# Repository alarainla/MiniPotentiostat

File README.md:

# MiniPotentiostat
This is repository for minimalistic open-source potentiostat for electrochemical sensing

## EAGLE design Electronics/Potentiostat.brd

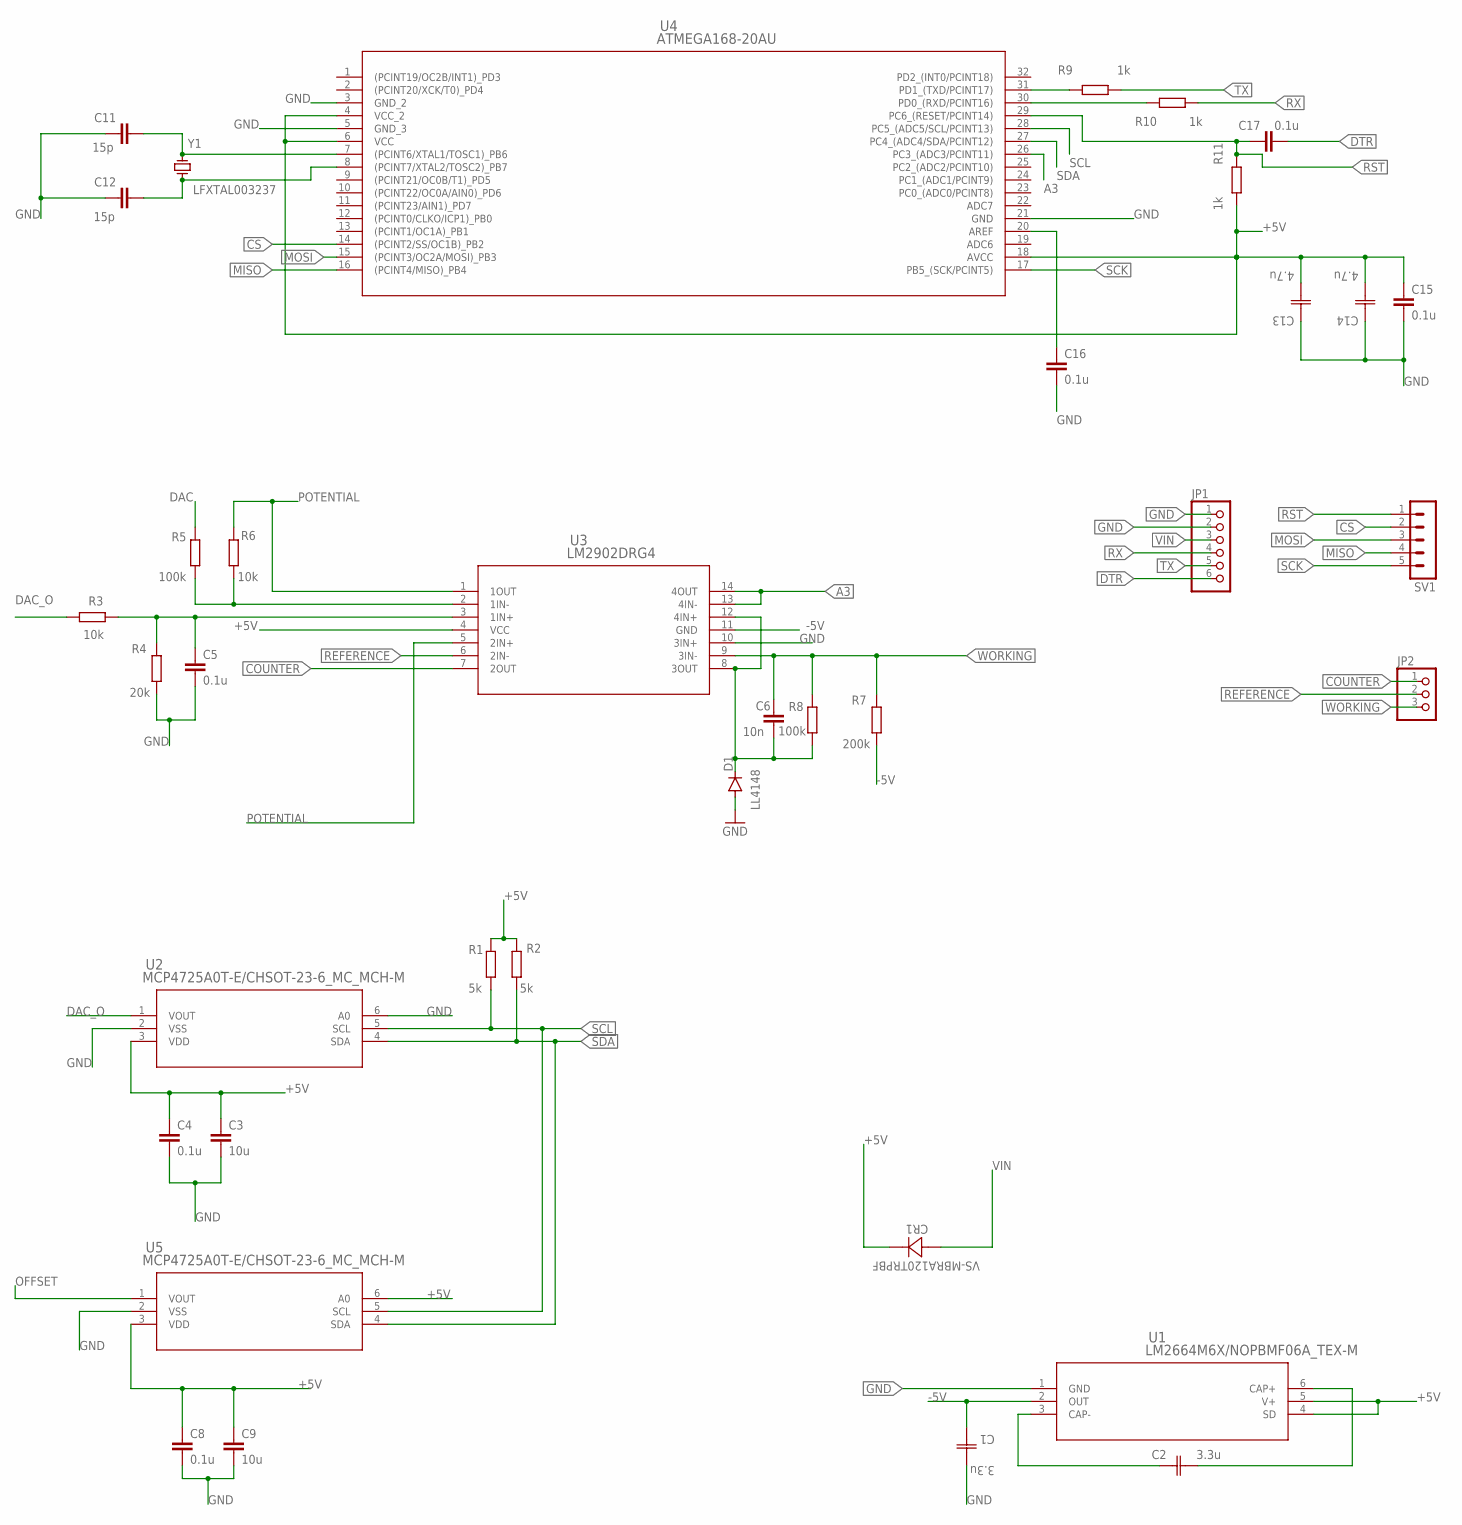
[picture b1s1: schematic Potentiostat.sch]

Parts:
C1, C2: 3.3u; CAP_293D_A_VIS-M
C3, C9: 10u; C0805
C4, C5, C8, C15, C16, C17: 0.1u; C0805
C6: 10n; C0805
C11, C12: 15p; C0805
C13, C14: 4.7u; CAP_293D_A_VIS-M
CR1: VS-MBRA120TRPBF; DIODE_SMA_VIS
D1: LL4148; SOD80C
JP1: PINHD-1X6CB; 1X06-CLEANBIG
JP2: PINHD-1X3CB; 1X03-CLEANBIG
R1, R2: 5k; R0805
R3, R6: 10k; R0805
R4: 20k; R0805
R5, R8: 100k; R0805
R7: 200k; R0805
R9, R10, R11: 1k; R0805
SV1: MA05-1
U1: LM2664M6X/NOPBMF06A_TEX-M; MF06A_TEX-M
U2, U5: MCP4725A0T-E/CHSOT-23-6_MC_MCH-M; SOT-23-6_MC_MCH-M
U3: LM2902DRG4; D14_TEX
U4: ATMEGA168-20AU; 32A_ATM
Y1: LFXTAL003237; XTAL1140X490X430N

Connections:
+5V: C3.1, C4.1, C8.1, C9.1, C13.2, C14.2, C15.1, CR1.1, R1.2, R2.2, R11.1, U1.4 (SD), U1.5 (V+), U2.3 (VDD), U3.4 (VCC), U4.4 (VCC_2), U4.6 (VCC), U4.18 (AVCC), U5.3 (VDD), U5.6 (A0)
-5V: C1.2, R7.1, U1.2 (OUT), U3.11 (GND)
A3: U3.13 (4IN-), U3.14 (4OUT), U4.26 (PC3_(ADC3/PCINT11))
COUNTER: JP2.1, U3.7 (2OUT)
CS: SV1.2, U4.14 ((PCINT2/SS/OC1B)_PB2)
DAC: R5.2
DAC_O: R3.2, U2.1 (VOUT)
DTR: C17.2, JP1.6
GND: C1.1, C3.2, C4.2, C5.2, C8.2, C9.2, C11.1, C12.1, C13.1, C14.1, C15.2, C16.2, D1.A, JP1.1, JP1.2, R4.1, U1.1 (GND), U2.2 (VSS), U2.6 (A0), U3.10 (3IN+), U4.3 (GND_2), U4.5 (GND_3), U4.21 (GND), U5.2 (VSS)
MISO: SV1.4, U4.16 ((PCINT4/MISO)_PB4)
MOSI: SV1.3, U4.15 ((PCINT3/OC2A/MOSI)_PB3)
unnamed: C6.2, D1.C, R8.1, U3.8 (3OUT), U3.12 (4IN+)
unnamed: C2.1, U1.3 (CAP-)
unnamed: C5.1, R3.1, R4.2, U3.3 (1IN+)
unnamed: R5.1, R6.1, U3.2 (1IN-)
unnamed: C11.2, U4.7 ((PCINT6/XTAL1/TOSC1)_PB6), Y1.2
unnamed: C2.2, U1.6 (CAP+)
unnamed: C12.2, U4.8 ((PCINT7/XTAL2/TOSC2)_PB7), Y1.1
unnamed: R9.2, U4.31 (PD1_(TXD/PCINT17))
unnamed: R10.2, U4.30 (PD0_(RXD/PCINT16))
unnamed: C16.1, U4.20 (AREF)
OFFSET: U5.1 (VOUT)
POTENTIAL: R6.2, U3.1 (1OUT), U3.5 (2IN+)
REFERENCE: JP2.2, U3.6 (2IN-)
RST: C17.1, R11.2, SV1.1, U4.29 (PC6_(RESET/PCINT14))
RX: JP1.4, R10.1
SCK: SV1.5, U4.17 (PB5_(SCK/PCINT5))
SCL: R1.1, U2.5 (SCL), U4.28 (PC5_(ADC5/SCL/PCINT13)), U5.5 (SCL)
SDA: R2.1, U2.4 (SDA), U4.27 (PC4_(ADC4/SDA/PCINT12)), U5.4 (SDA)
TX: JP1.5, R9.1
VIN: CR1.2, JP1.3
WORKING: C6.1, JP2.3, R7.2, R8.2, U3.9 (3IN-)

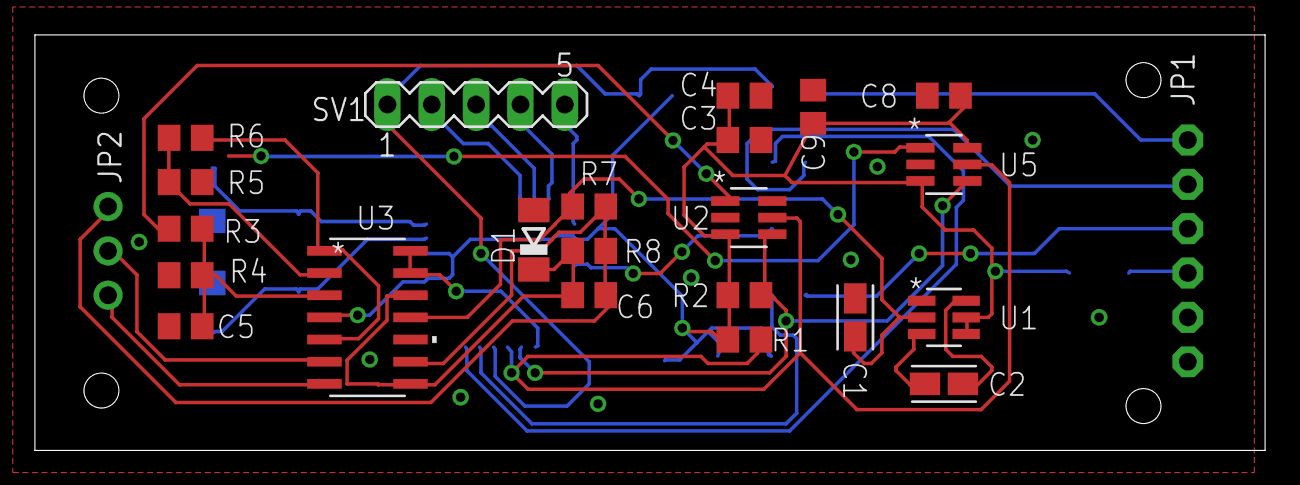
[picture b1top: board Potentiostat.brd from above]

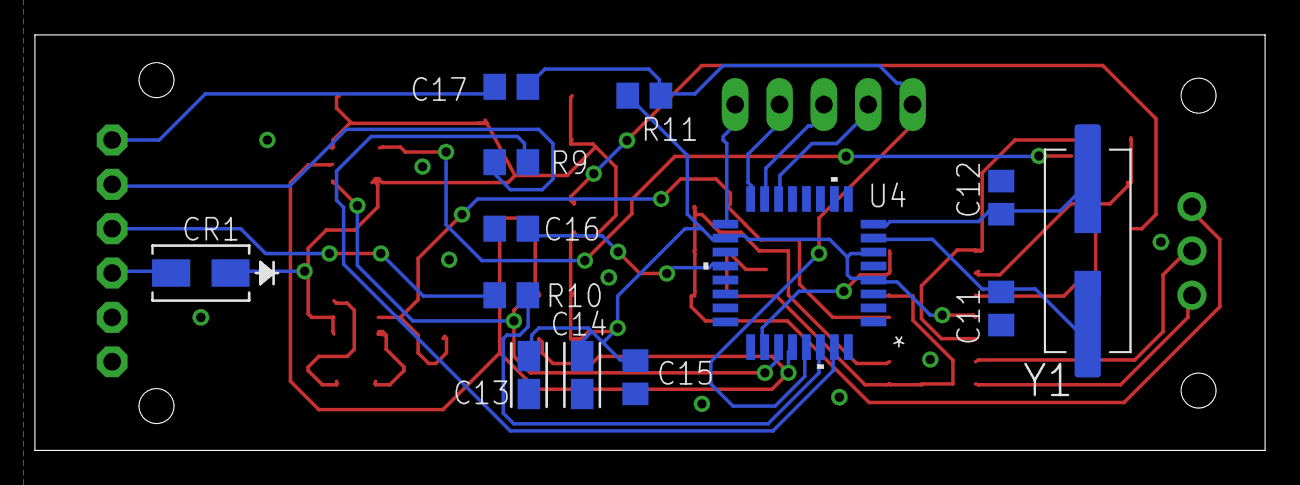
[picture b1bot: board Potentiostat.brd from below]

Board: 2 copper layers, 70.5 x 23.8 mm, 37 parts (13 on the bottom side), 30 nets.

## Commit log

2021-10-17 Add files via upload
    Control app
2021-10-17 Potentiostat app
2021-10-17 Electronics design
2021-10-17 Firmware (Arduino)

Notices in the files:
parts and their libraries:
COPYRIGHT: Copyright (C) 2015 Accelerated Designs. All rights reserved
